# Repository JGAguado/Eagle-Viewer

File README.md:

# Eagle-Viewer
Script for reading Eagle's .brd files and plotting it into 2D/3D graphics.

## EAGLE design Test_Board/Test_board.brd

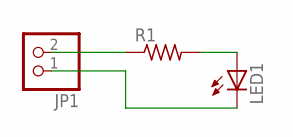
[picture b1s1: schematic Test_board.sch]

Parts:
JP1: PINHD-1X2; 1X02
LED1: LEDSML1206; SML1206
R1: R-US_M1206; M1206

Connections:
unnamed: LED1.A, R1.2
unnamed: JP1.2, R1.1
unnamed: JP1.1, LED1.C

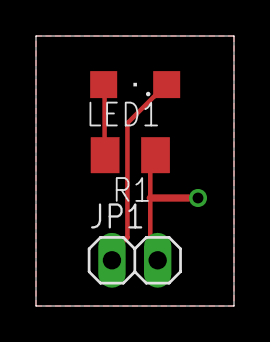
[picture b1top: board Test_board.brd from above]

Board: 2 copper layers, 11.0 x 15.0 mm, 3 parts (0 on the bottom side), 3 nets.

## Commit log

2020-12-22 Updated Eagle-viewer (development stopped)
